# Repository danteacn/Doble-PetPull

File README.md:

# Doble-PetPull

- Version doble imitado de PetPull-2 de Zneipas (sapienZ). https://3deshnik.ru/forum/viewtopic.php?f=37&t=986&p=46411#p46411
- Algunas ideas tomadas de: https://github.com/Reloader/PETCTL

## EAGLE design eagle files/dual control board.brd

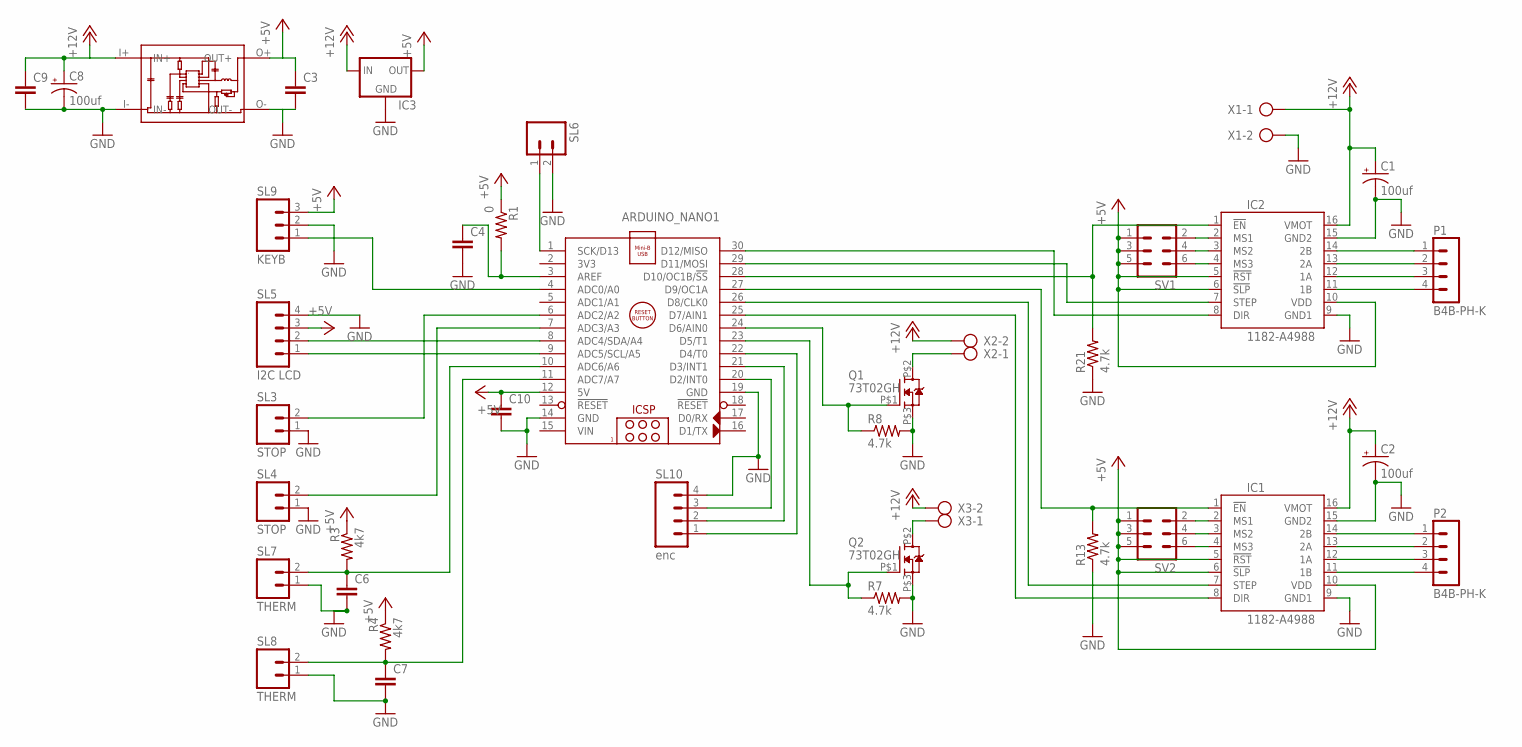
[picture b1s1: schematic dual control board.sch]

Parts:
ARDUINO_NANO1: ARDUINO_NANO
C1, C2, C8: 100uf; E3,5-8
C3, C4, C6, C7, C9, C10: C-EU050-024X044; C050-024X044
IC1, IC2: 1182-A4988; A4988
IC3: 78XXL
P1, P2: B4B-PH-K
Q1, Q2: 73T02GH; TO252
R1: 0; 0204/5
R3, R4: 4k7; 0204/5
R7, R8, R13, R21: 4.7k; 0204/5
SL3, SL4: STOP; 02P
SL5: I2C LCD; 04P
SL6: M02; 02P
SL7, SL8: THERM; 02P
SL9: KEYB; 03P
SL10: enc; 04P
SV1, SV2: MA03-2
U$1: MINI360
X1, X2, X3: AK500/2

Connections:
+5V: ARDUINO_NANO1.12 (5V), C3.1, C10.1, IC1.5 (!RST), IC1.6 (!SLP), IC1.10 (VDD), IC2.5 (!RST), IC2.6 (!SLP), IC2.10 (VDD), IC3.OUT, R1.1, R3.1, R4.1, SL5.3, SL9.3, SV1.1, SV1.3, SV1.5, SV2.1, SV2.3, SV2.5, U$1.O+ (OUT+)
+12V: C1.+, C2.+, C8.+, C9.1, IC1.16 (VMOT), IC2.16 (VMOT), IC3.IN, U$1.I+ (IN+), X1.1, X2.2, X3.2
GND: ARDUINO_NANO1.14 (GND), ARDUINO_NANO1.19 (GND), C1.-, C2.-, C3.2, C4.2, C6.2, C7.2, C8.-, C9.2, C10.2, IC1.9 (GND1), IC1.15 (GND2), IC2.9 (GND1), IC2.15 (GND2), IC3.GND, Q1.P$3 (S), Q2.P$3 (S), R7.2, R8.2, R13.1, R21.1, SL3.1, SL4.1, SL5.4, SL6.2, SL7.1, SL8.1, SL9.2, SL10.4, U$1.I- (IN-), U$1.O- (OUT-), X1.2
unnamed: ARDUINO_NANO1.9 (ADC5/SCL/A5), SL5.1
unnamed: ARDUINO_NANO1.8 (ADC4/SDA/A4), SL5.2
unnamed: ARDUINO_NANO1.23 (D5/T1), Q2.P$1 (G), R7.1
unnamed: ARDUINO_NANO1.6 (ADC2/A2), SL3.2
unnamed: ARDUINO_NANO1.24 (D6/AIN0), Q1.P$1 (G), R8.1
unnamed: ARDUINO_NANO1.4 (ADC0/A0), SL9.1
unnamed: ARDUINO_NANO1.3 (AREF), C4.1, R1.2
unnamed: IC2.14 (2B), P1.1
unnamed: IC2.13 (2A), P1.2
unnamed: IC2.12 (1A), P1.3
unnamed: IC2.11 (1B), P1.4
unnamed: IC1.14 (2B), P2.1
unnamed: IC1.13 (2A), P2.2
unnamed: IC1.12 (1A), P2.3
unnamed: IC1.11 (1B), P2.4
unnamed: ARDUINO_NANO1.7 (ADC3/A3), SL4.2
unnamed: ARDUINO_NANO1.10 (ADC6/A6), C6.1, R3.2, SL7.2
unnamed: Q1.P$2 (D), X2.1
unnamed: Q2.P$2 (D), X3.1
unnamed: ARDUINO_NANO1.11 (ADC7/A7), C7.1, R4.2, SL8.2
unnamed: IC1.2 (MS1), SV2.2
unnamed: IC2.2 (MS1), SV1.2
unnamed: ARDUINO_NANO1.28 (D10/OC1B/!SS), IC2.1 (!EN), R21.2
unnamed: IC2.3 (MS2), SV1.4
unnamed: ARDUINO_NANO1.25 (D7/AIN1), IC1.8 (DIR)
unnamed: ARDUINO_NANO1.26 (D8/CLK0), IC1.7 (STEP)
unnamed: ARDUINO_NANO1.27 (D9/OC1A), IC1.1 (!EN), R13.2
unnamed: IC2.4 (MS3), SV1.6
unnamed: ARDUINO_NANO1.1 (SCK/D13), SL6.1
unnamed: ARDUINO_NANO1.30 (D12/MISO), IC2.8 (DIR)
unnamed: ARDUINO_NANO1.20 (D2/INT0), SL10.3
unnamed: ARDUINO_NANO1.22 (D4/T0), SL10.1
unnamed: ARDUINO_NANO1.29 (D11/MOSI), IC2.7 (STEP)
unnamed: ARDUINO_NANO1.21 (D3/INT1), SL10.2
unnamed: IC1.3 (MS2), SV2.4
unnamed: IC1.4 (MS3), SV2.6
VIN: ARDUINO_NANO1.15 (VIN)

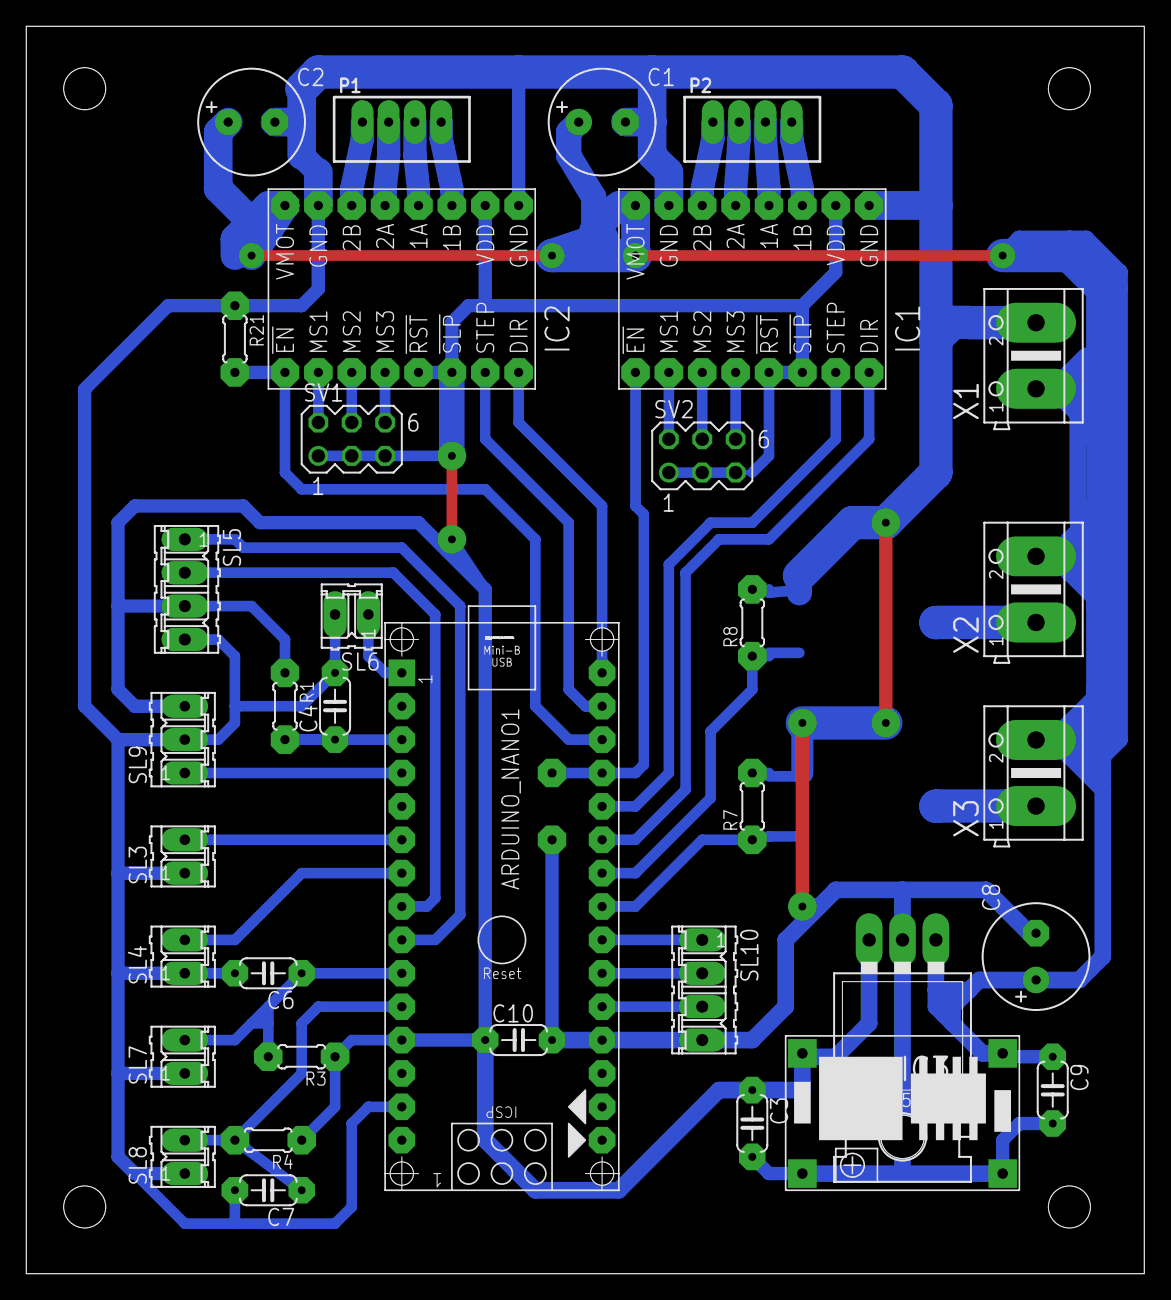
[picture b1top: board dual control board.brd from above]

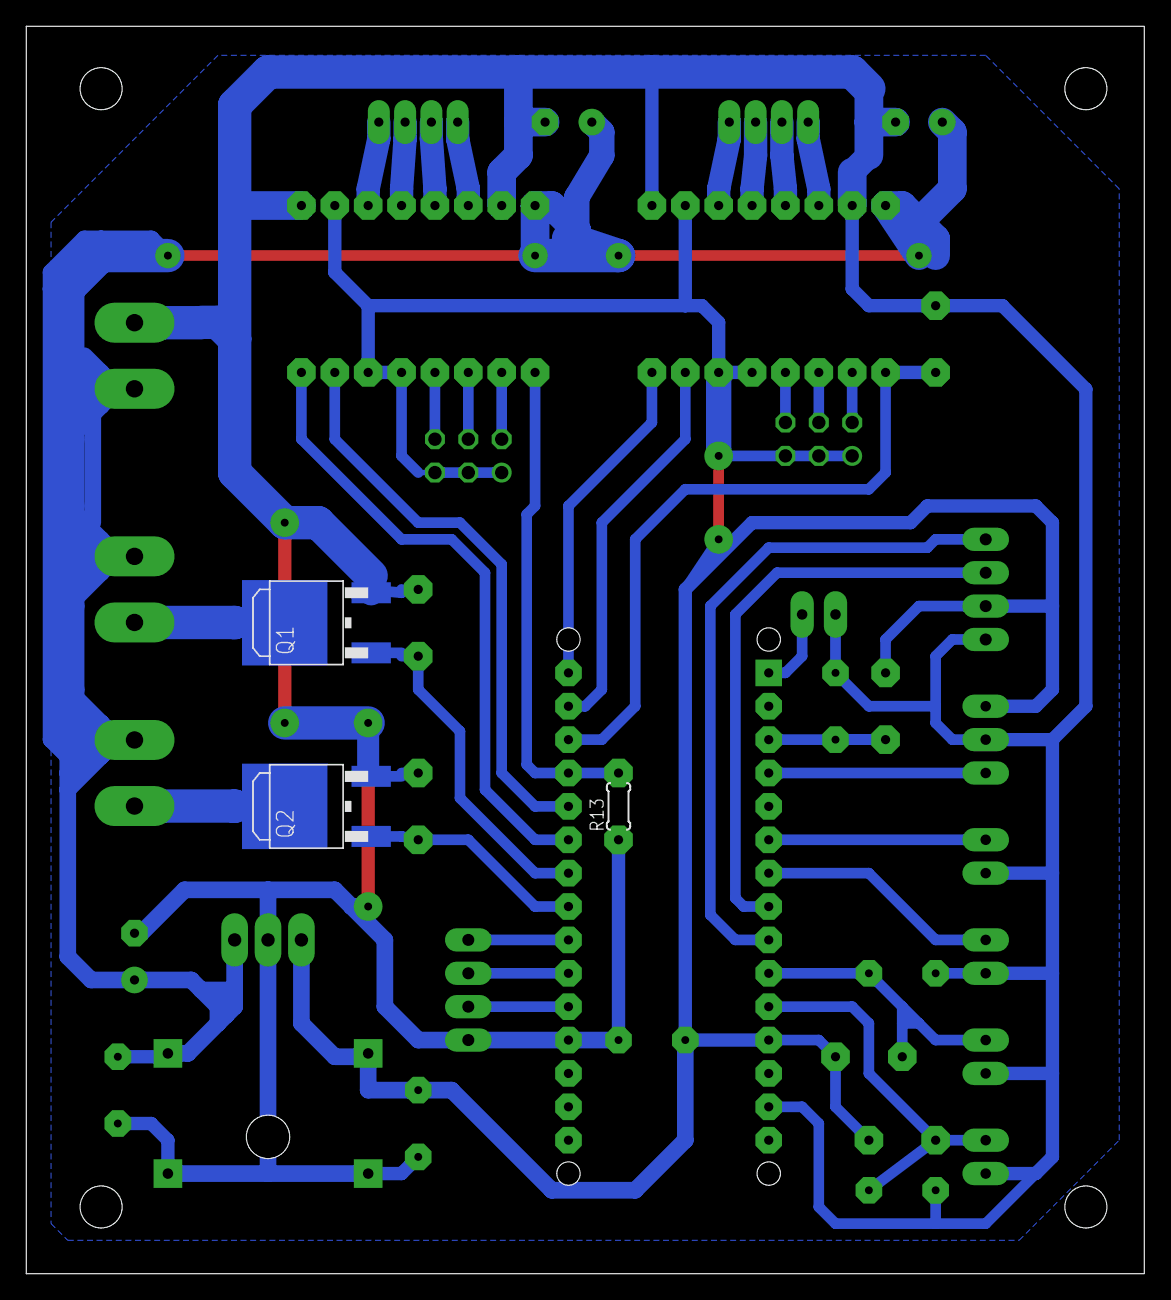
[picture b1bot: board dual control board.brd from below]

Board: 2 copper layers, 85.1 x 94.9 mm, 38 parts (3 on the bottom side), 39 nets.

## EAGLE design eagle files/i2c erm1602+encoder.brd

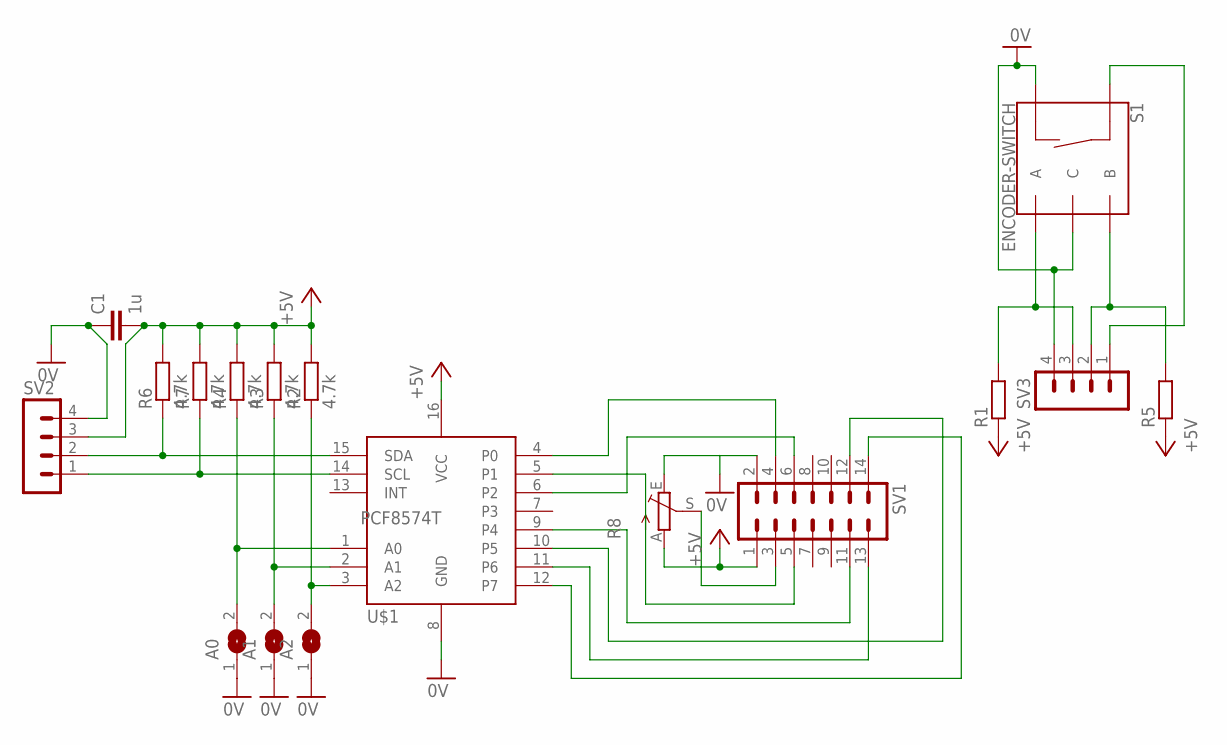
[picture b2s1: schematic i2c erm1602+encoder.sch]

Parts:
A0, A1, A2: SJ
C1: 1u; C1206K
R1, R5: R-EU_0204/5; 0204/5
R2, R3, R4, R6, R7: 4.7k; 0204/5
R8: TRIM_EU-B25P; B25P
S1: ENCODER-SWITCH; ROTARY_ENC_PLAIN
SV1: MA07-2
SV2, SV3: MA04-1
U$1: PCF8574T; SOT162

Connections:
0V: A0.1, A1.1, A2.1, C1.1, R8.E, S1.C, S1.SW-, SV1.2, SV2.4, SV3.4, U$1.8 (GND)
+5V: C1.2, R1.1, R2.2, R3.2, R4.2, R5.1, R6.2, R7.2, R8.A, SV1.1, SV2.3, U$1.16 (VCC)
unnamed: A0.2, R4.1, U$1.1 (A0)
unnamed: A1.2, R3.1, U$1.2 (A1)
unnamed: A2.2, R2.1, U$1.3 (A2)
unnamed: SV1.4, U$1.4 (P0)
unnamed: R6.1, SV2.2, U$1.15 (SDA)
unnamed: R7.1, SV2.1, U$1.14 (SCL)
unnamed: SV1.5, U$1.5 (P1)
unnamed: SV1.14, U$1.12 (P7)
unnamed: SV1.13, U$1.11 (P6)
unnamed: SV1.12, U$1.10 (P5)
unnamed: SV1.11, U$1.9 (P4)
unnamed: SV1.6, U$1.6 (P2)
unnamed: R1.2, S1.A, SV3.3
unnamed: R8.S, SV1.3
unnamed: R5.2, S1.B, SV3.2
unnamed: S1.SW+, SV3.1

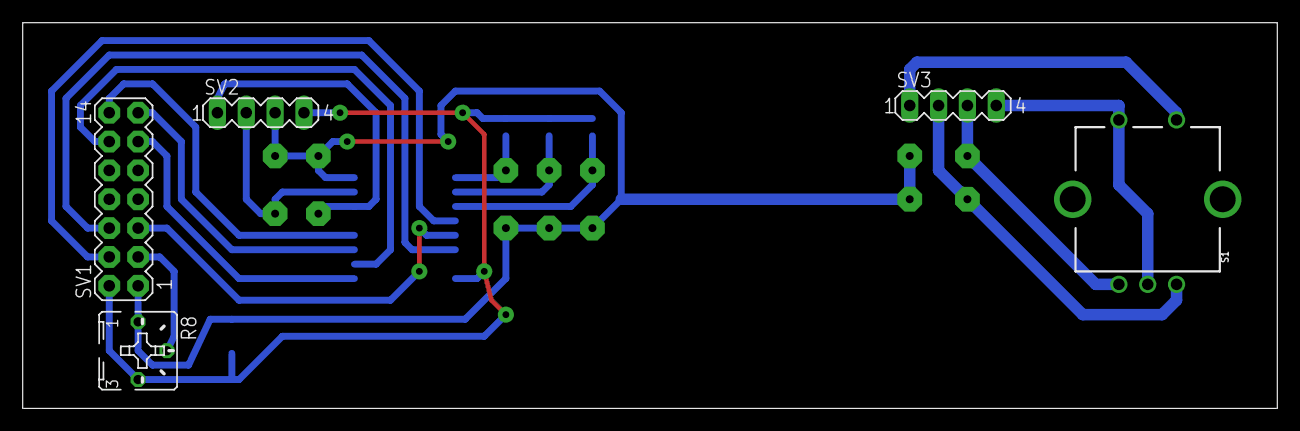
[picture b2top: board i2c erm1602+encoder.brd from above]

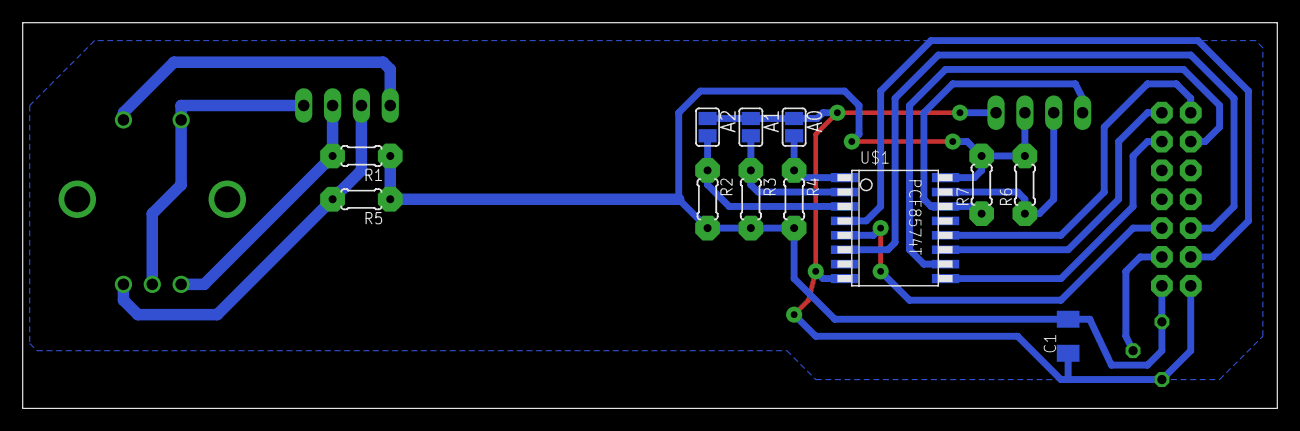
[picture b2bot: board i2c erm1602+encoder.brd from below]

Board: 2 copper layers, 110.5 x 34.0 mm, 17 parts (12 on the bottom side), 18 nets.

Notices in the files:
parts and their libraries:
con-jst-ph: Copyright (C) 2016, Bob Starr
SparkFun-Switches: Licensing: Creative Commons ShareAlike 4.0 International - https://creativecommons.org/licenses/by-sa/4.0
